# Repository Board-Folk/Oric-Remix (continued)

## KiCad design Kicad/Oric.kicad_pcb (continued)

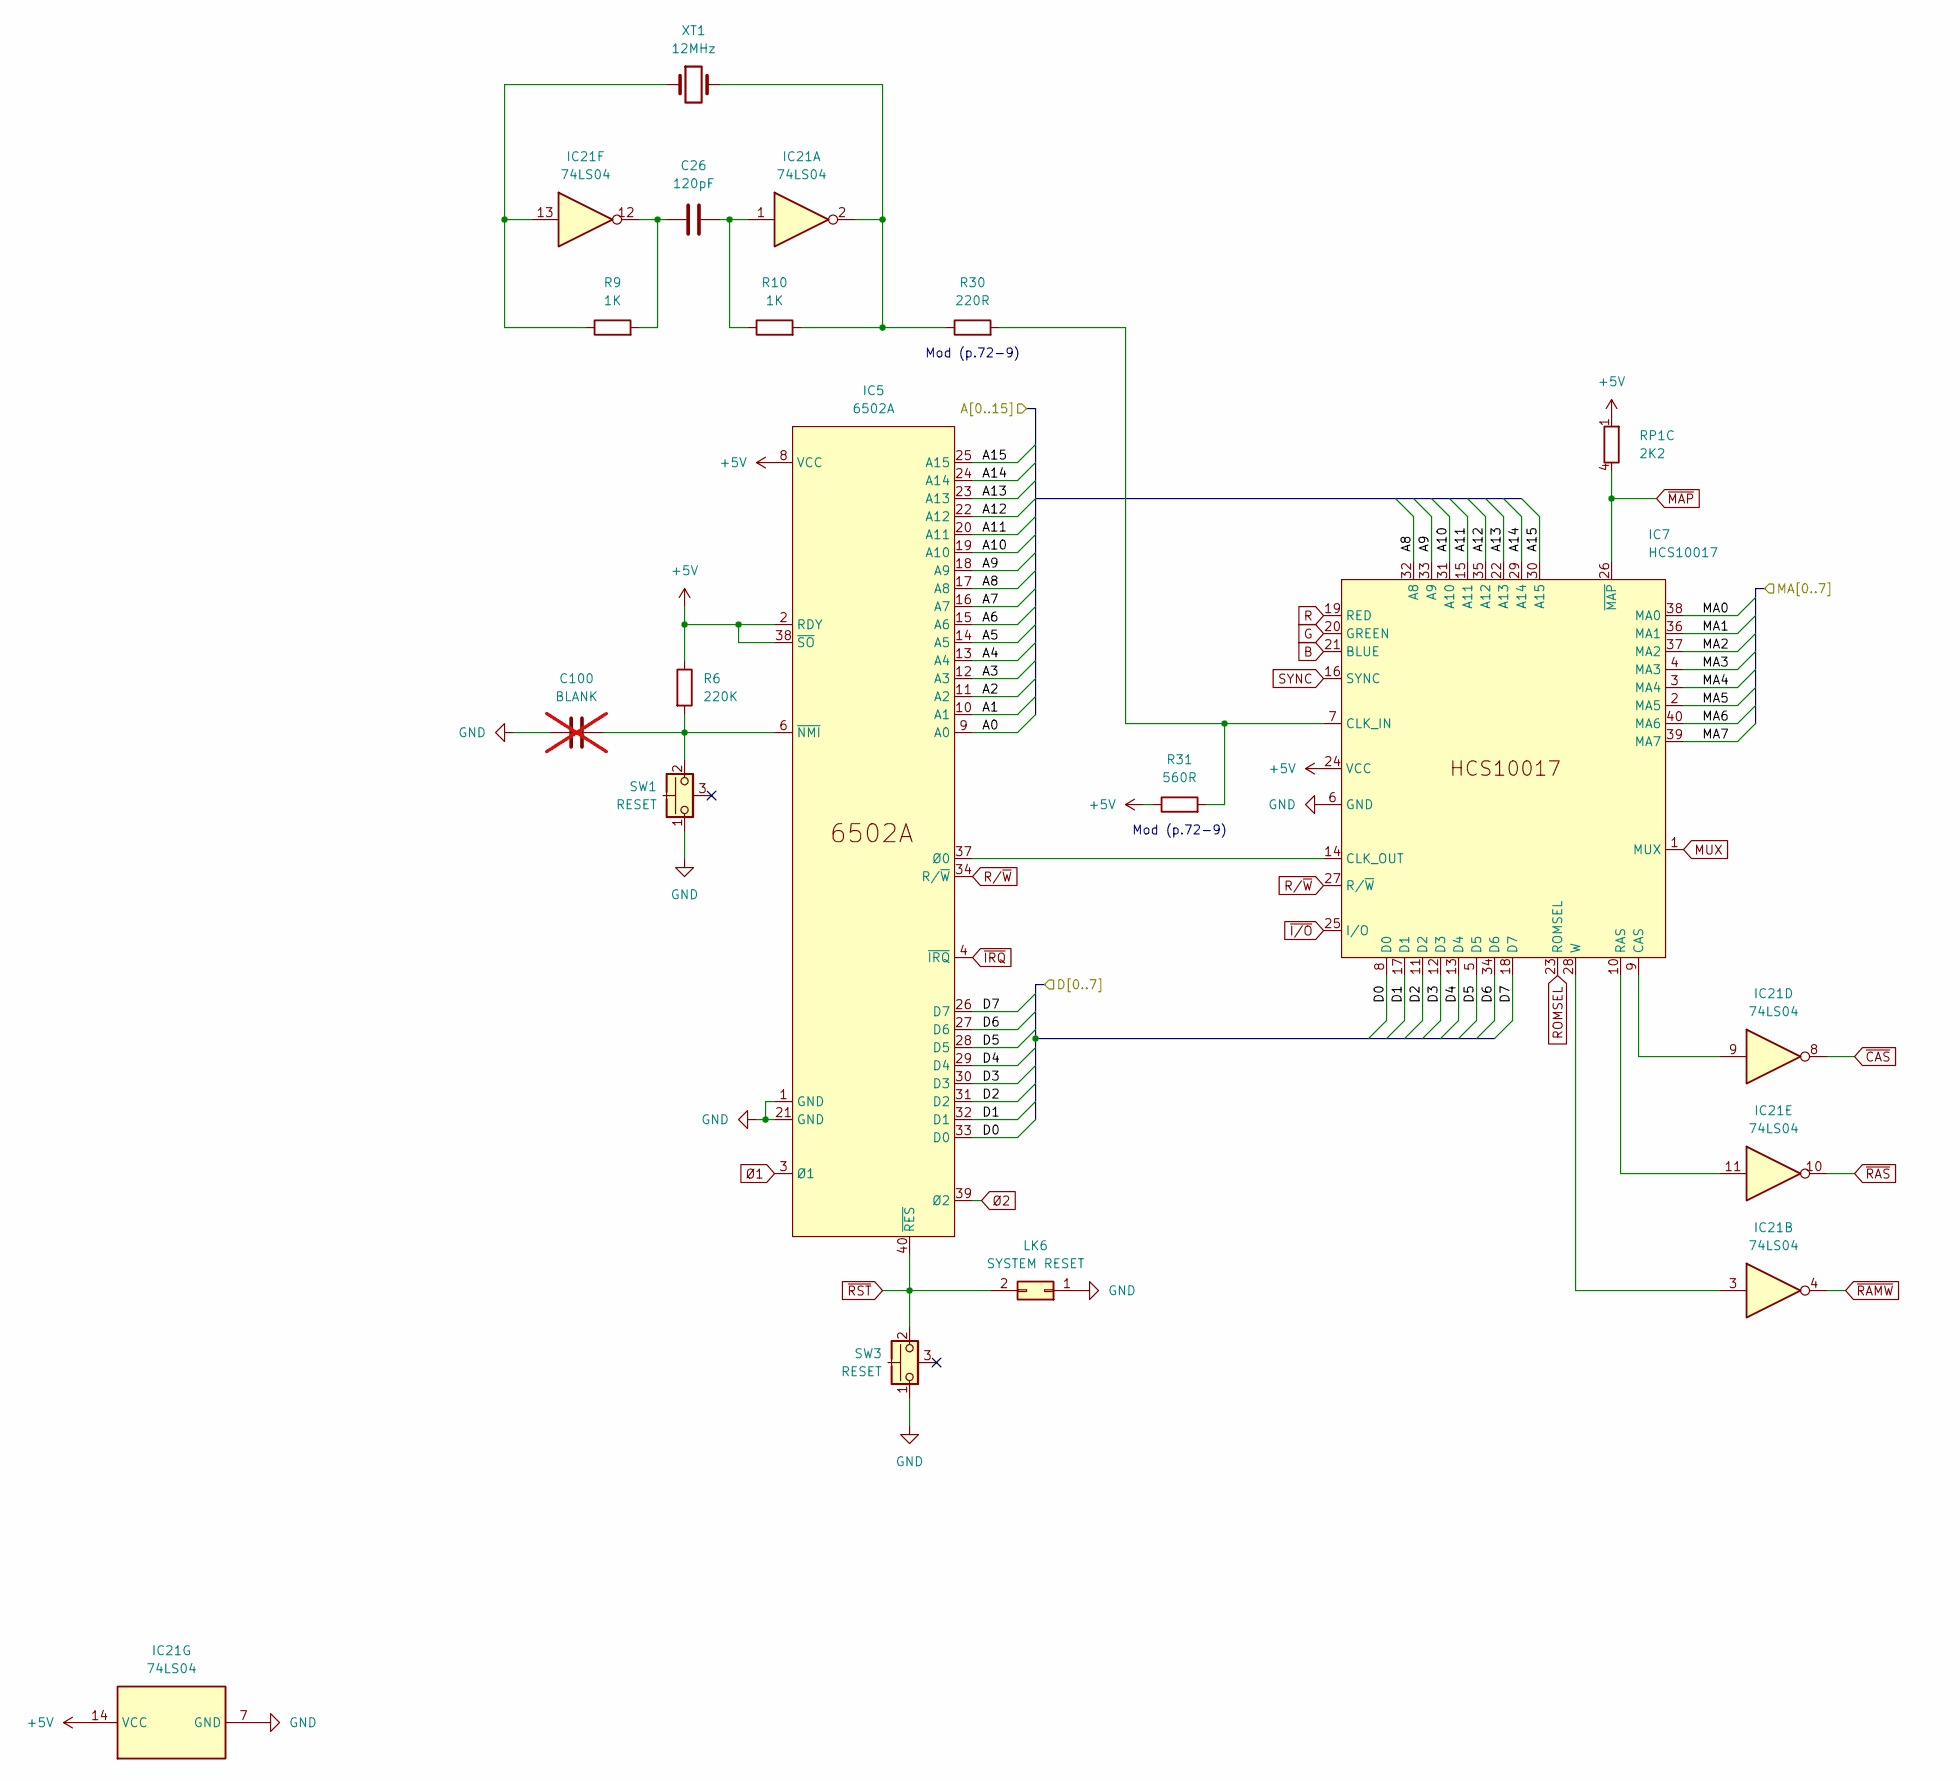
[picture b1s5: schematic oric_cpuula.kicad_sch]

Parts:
C26: 120pF; Ceramic Capacitor 5.00mm
C100: BLANK; Ceramic Capacitor 5.00mm_Blank; not fitted
IC5: 6502A; DIP-40_W15.24mm
IC7: HCS10017; DIP-40_W15.24mm
IC21: 74LS04; DIP-14_W7.62mm
LK6: SYSTEM RESET; PinHeader_1x02_P2.54mm
R6: 220K; Resistor 10.16mm
R9, R10: 1K; Resistor 10.16mm
R30: 220R; Resistor 10.16mm
R31: 560R; Resistor 10.16mm
RP1: 2K2; R_Array_SIP8_Bussed
SW1: RESET; Push Switch
SW3: RESET; Push Switch Simple
XT1: 12MHz; Crystal

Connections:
+5V: IC5.2 (RDY), IC5.8 (VCC), IC5.38 (~SO), IC7.24 (VCC), IC21.14 (VCC), R6.1, R31.1, RP1.1 (R1); also elsewhere on the board
/CPU and ULA/A0: IC5.9 (A0); also elsewhere on the board
/CPU and ULA/A1: IC5.10 (A1); also elsewhere on the board
/CPU and ULA/A2: IC5.11 (A2); also elsewhere on the board
/CPU and ULA/A3: IC5.12 (A3); also elsewhere on the board
/CPU and ULA/A4: IC5.13 (A4); also elsewhere on the board
/CPU and ULA/A5: IC5.14 (A5); also elsewhere on the board
/CPU and ULA/A6: IC5.15 (A6); also elsewhere on the board
/CPU and ULA/A7: IC5.16 (A7); also elsewhere on the board
/CPU and ULA/A8: IC5.17 (A8), IC7.32 (A8); also elsewhere on the board
/CPU and ULA/A9: IC5.18 (A9), IC7.33 (A9); also elsewhere on the board
/CPU and ULA/A10: IC5.19 (A10), IC7.31 (A10); also elsewhere on the board
/CPU and ULA/A11: IC5.20 (A11), IC7.15 (A11); also elsewhere on the board
/CPU and ULA/A12: IC5.22 (A12), IC7.35 (A12); also elsewhere on the board
/CPU and ULA/A13: IC5.23 (A13), IC7.22 (A13); also elsewhere on the board
/CPU and ULA/A14: IC5.24 (A14), IC7.29 (A14); also elsewhere on the board
/CPU and ULA/A15: IC5.25 (A15), IC7.30 (A15); also elsewhere on the board
/CPU and ULA/D0: IC5.33 (D0), IC7.8 (D0); also elsewhere on the board
/CPU and ULA/D1: IC5.32 (D1), IC7.17 (D1); also elsewhere on the board
/CPU and ULA/D2: IC5.31 (D2), IC7.11 (D2); also elsewhere on the board
/CPU and ULA/D3: IC5.30 (D3), IC7.12 (D3); also elsewhere on the board
/CPU and ULA/D4: IC5.29 (D4), IC7.13 (D4); also elsewhere on the board
/CPU and ULA/D5: IC5.28 (D5), IC7.5 (D5); also elsewhere on the board
/CPU and ULA/D6: IC5.27 (D6), IC7.34 (D6); also elsewhere on the board
/CPU and ULA/D7: IC5.26 (D7), IC7.18 (D7); also elsewhere on the board
/CPU and ULA/MA0: IC7.38 (MA0); also elsewhere on the board
/CPU and ULA/MA1: IC7.36 (MA1); also elsewhere on the board
/CPU and ULA/MA2: IC7.37 (MA2); also elsewhere on the board
/CPU and ULA/MA3: IC7.4 (MA3); also elsewhere on the board
/CPU and ULA/MA4: IC7.3 (MA4); also elsewhere on the board
/CPU and ULA/MA5: IC7.2 (MA5); also elsewhere on the board
/CPU and ULA/MA6: IC7.40 (MA6); also elsewhere on the board
/CPU and ULA/MA7: IC7.39 (MA7); also elsewhere on the board
B: IC7.21 (BLUE); also elsewhere on the board
G: IC7.20 (GREEN); also elsewhere on the board
GND: C100.1, IC5.1 (GND), IC5.21 (GND), IC7.6 (GND), IC21.7 (GND), LK6.1, SW1.1, SW3.1; also elsewhere on the board
MUX: IC7.1 (MUX); also elsewhere on the board
unnamed: C26.1, IC21.12, R9.2
unnamed: C26.2, IC21.1, R10.1
unnamed: C100.2, IC5.6 (~NMI), R6.2, SW1.2
unnamed: IC5.37 (Ø0), IC7.14 (CLK_OUT)
unnamed: IC7.9 (CAS), IC21.9
unnamed: IC7.7 (CLK_IN), R30.2, R31.2
unnamed: IC7.10 (RAS), IC21.11
unnamed: IC7.28 (W), IC21.3
unnamed: IC21.2, R10.2, R30.1, XT1.2
unnamed: IC21.13, R9.1, XT1.1
R: IC7.19 (RED); also elsewhere on the board
ROMSEL: IC7.23 (ROMSEL); also elsewhere on the board
R/~W: IC5.34 (R/~W), IC7.27 (R/~W); also elsewhere on the board
SYNC: IC7.16 (SYNC); also elsewhere on the board
~CAS: IC21.8; also elsewhere on the board
~IRQ: IC5.4 (~IRQ); also elsewhere on the board
~I/O: IC7.25 (I/O); also elsewhere on the board
~MAP: IC7.26 (~MAP), RP1.4 (R3.2); also elsewhere on the board
~RAMW: IC21.4; also elsewhere on the board
~RAS: IC21.10; also elsewhere on the board
~RST: IC5.40 (~RES), LK6.2, SW3.2; also elsewhere on the board
Ø1: IC5.3 (Ø1); also elsewhere on the board
Ø2: IC5.39 (Ø2); also elsewhere on the board

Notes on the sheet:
Mod (p.72-9)

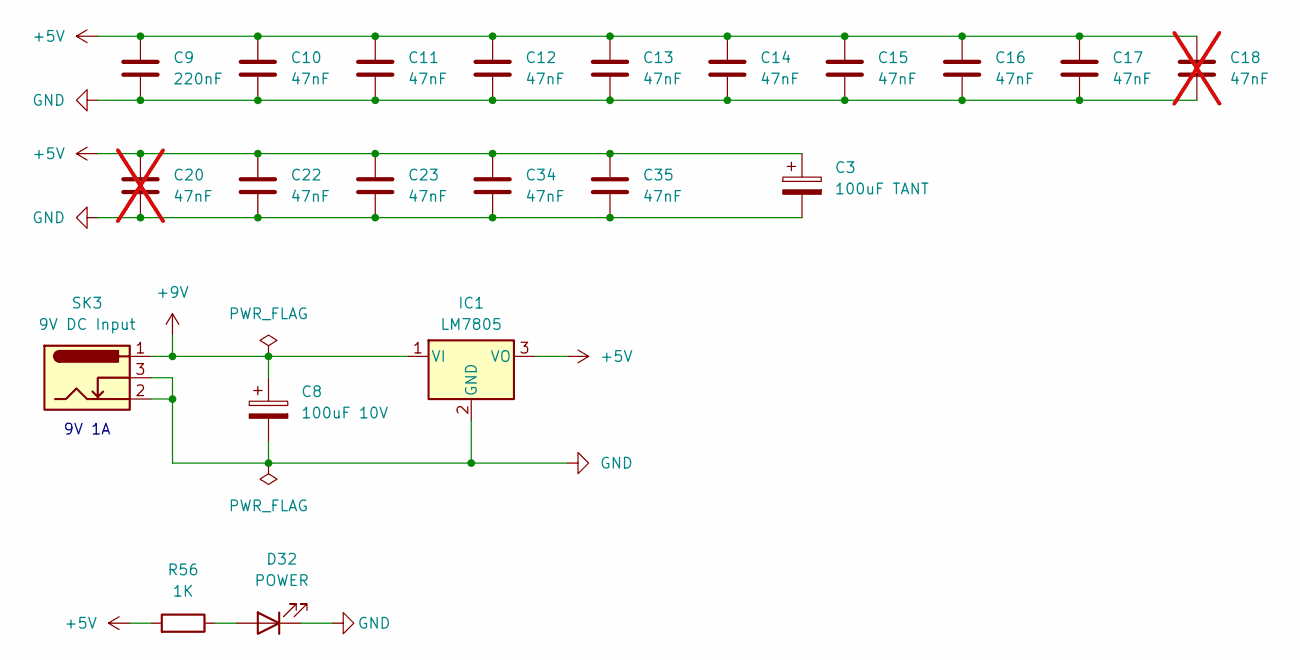
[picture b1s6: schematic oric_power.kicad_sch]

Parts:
C3: 100uF TANT; Tantalum Capacitor 5.00mm
C8: 100uF 10V; Electrolytic Capacitor 5.00mm
C9: 220nF; Ceramic Capacitor 5.00mm
C10, C11, C12, C13, C14, C15, C16, C17, C22, C23, C34, C35: 47nF; Ceramic Capacitor 5.00mm
C18, C20: 47nF; Ceramic Capacitor 5.00mm; not fitted
D32: POWER; LED_D3.0mm
IC1: LM7805; IC1 7805
R56: 1K; Resistor 10.16mm
SK3: 9V DC Input; SK3 Barrel Jack

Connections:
+5V: C3.1, C9.1, C10.1, C11.1, C12.1, C13.1, C14.1, C15.1, C16.1, C17.1, C18.1, C20.1, C22.1, C23.1, C34.1, C35.1, IC1.3 (VO), R56.2; also elsewhere on the board
+9V: C8.1, IC1.1 (VI), SK3.1; also elsewhere on the board
GND: C3.2, C8.2, C9.2, C10.2, C11.2, C12.2, C13.2, C14.2, C15.2, C16.2, C17.2, C18.2, C20.2, C22.2, C23.2, C34.2, C35.2, D32.1 (K), IC1.2 (GND), SK3.2, SK3.3; also elsewhere on the board
unnamed: D32.2 (A), R56.1

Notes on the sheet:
9V 1A

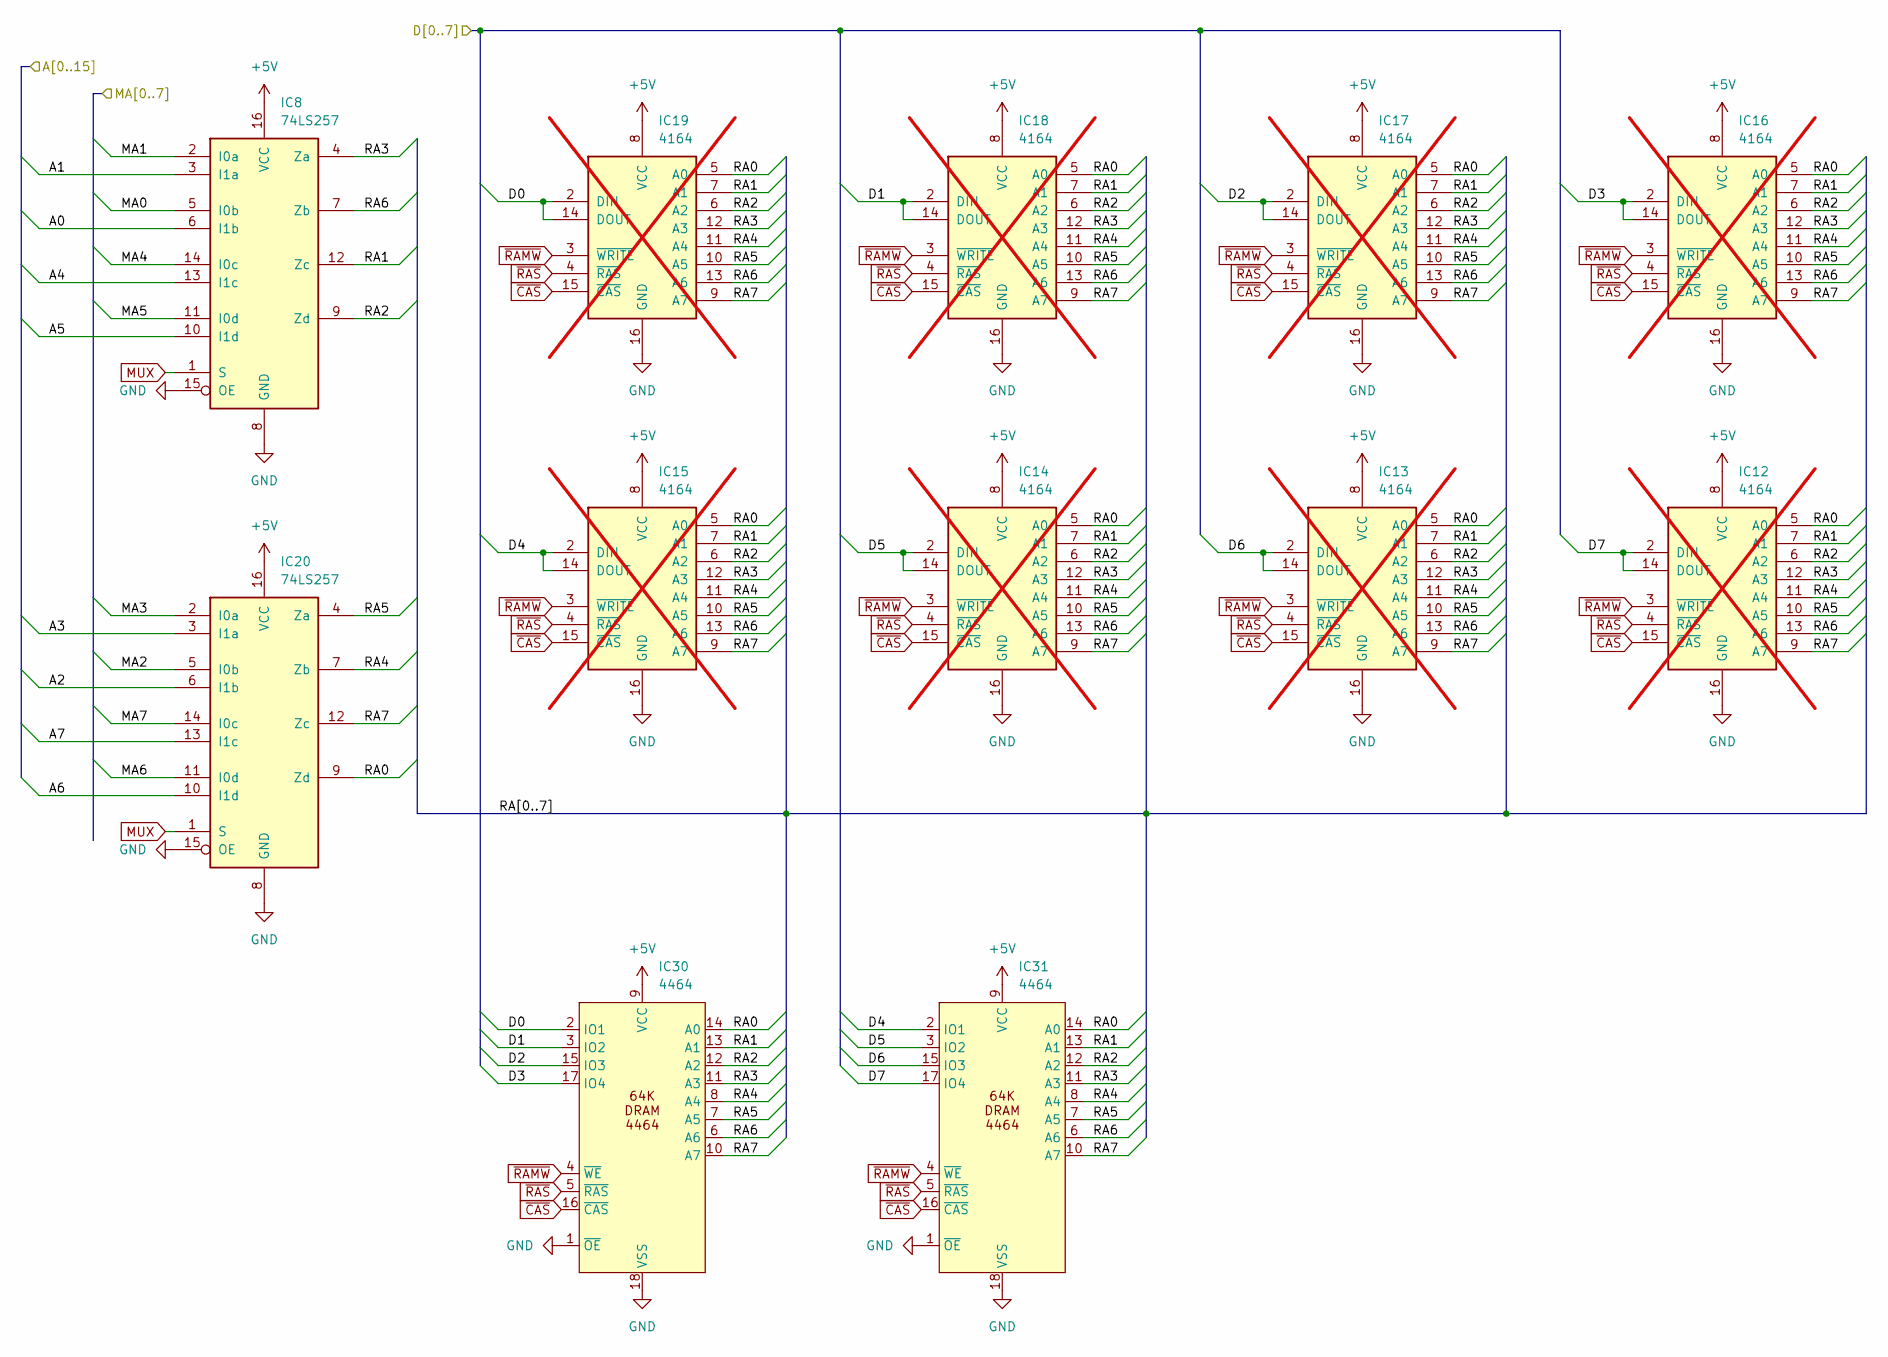
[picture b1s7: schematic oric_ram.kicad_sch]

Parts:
IC8, IC20: 74LS257; DIP-16_W7.62mm
IC12, IC13, IC14, IC15, IC16, IC17, IC18, IC19: 4164; DIP-16_W7.62mm; not fitted
IC30, IC31: 4464; DIP-18_W7.62mm

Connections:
+5V: IC8.16 (VCC), IC12.8 (VCC), IC13.8 (VCC), IC14.8 (VCC), IC15.8 (VCC), IC16.8 (VCC), IC17.8 (VCC), IC18.8 (VCC), IC19.8 (VCC), IC20.16 (VCC), IC30.9 (VCC), IC31.9 (VCC); also elsewhere on the board
/CPU and ULA/A0: IC8.6 (I1b); also elsewhere on the board
/CPU and ULA/A1: IC8.3 (I1a); also elsewhere on the board
/CPU and ULA/A2: IC20.6 (I1b); also elsewhere on the board
/CPU and ULA/A3: IC20.3 (I1a); also elsewhere on the board
/CPU and ULA/A4: IC8.13 (I1c); also elsewhere on the board
/CPU and ULA/A5: IC8.10 (I1d); also elsewhere on the board
/CPU and ULA/A6: IC20.10 (I1d); also elsewhere on the board
/CPU and ULA/A7: IC20.13 (I1c); also elsewhere on the board
/CPU and ULA/D0: IC19.2 (DIN), IC19.14 (DOUT), IC30.2 (IO1); also elsewhere on the board
/CPU and ULA/D1: IC18.2 (DIN), IC18.14 (DOUT), IC30.3 (IO2); also elsewhere on the board
/CPU and ULA/D2: IC17.2 (DIN), IC17.14 (DOUT), IC30.15 (IO3); also elsewhere on the board
/CPU and ULA/D3: IC16.2 (DIN), IC16.14 (DOUT), IC30.17 (IO4); also elsewhere on the board
/CPU and ULA/D4: IC15.2 (DIN), IC15.14 (DOUT), IC31.2 (IO1); also elsewhere on the board
/CPU and ULA/D5: IC14.2 (DIN), IC14.14 (DOUT), IC31.3 (IO2); also elsewhere on the board
/CPU and ULA/D6: IC13.2 (DIN), IC13.14 (DOUT), IC31.15 (IO3); also elsewhere on the board
/CPU and ULA/D7: IC12.2 (DIN), IC12.14 (DOUT), IC31.17 (IO4); also elsewhere on the board
/CPU and ULA/MA0: IC8.5 (I0b); also elsewhere on the board
/CPU and ULA/MA1: IC8.2 (I0a); also elsewhere on the board
/CPU and ULA/MA2: IC20.5 (I0b); also elsewhere on the board
/CPU and ULA/MA3: IC20.2 (I0a); also elsewhere on the board
/CPU and ULA/MA4: IC8.14 (I0c); also elsewhere on the board
/CPU and ULA/MA5: IC8.11 (I0d); also elsewhere on the board
/CPU and ULA/MA6: IC20.11 (I0d); also elsewhere on the board
/CPU and ULA/MA7: IC20.14 (I0c); also elsewhere on the board
/RAM/RA0: IC12.5 (A0), IC13.5 (A0), IC14.5 (A0), IC15.5 (A0), IC16.5 (A0), IC17.5 (A0), IC18.5 (A0), IC19.5 (A0), IC20.9 (Zd), IC30.14 (A0), IC31.14 (A0)
/RAM/RA1: IC8.12 (Zc), IC12.7 (A1), IC13.7 (A1), IC14.7 (A1), IC15.7 (A1), IC16.7 (A1), IC17.7 (A1), IC18.7 (A1), IC19.7 (A1), IC30.13 (A1), IC31.13 (A1)
/RAM/RA2: IC8.9 (Zd), IC12.6 (A2), IC13.6 (A2), IC14.6 (A2), IC15.6 (A2), IC16.6 (A2), IC17.6 (A2), IC18.6 (A2), IC19.6 (A2), IC30.12 (A2), IC31.12 (A2)
/RAM/RA3: IC8.4 (Za), IC12.12 (A3), IC13.12 (A3), IC14.12 (A3), IC15.12 (A3), IC16.12 (A3), IC17.12 (A3), IC18.12 (A3), IC19.12 (A3), IC30.11 (A3), IC31.11 (A3)
/RAM/RA4: IC12.11 (A4), IC13.11 (A4), IC14.11 (A4), IC15.11 (A4), IC16.11 (A4), IC17.11 (A4), IC18.11 (A4), IC19.11 (A4), IC20.7 (Zb), IC30.8 (A4), IC31.8 (A4)
/RAM/RA5: IC12.10 (A5), IC13.10 (A5), IC14.10 (A5), IC15.10 (A5), IC16.10 (A5), IC17.10 (A5), IC18.10 (A5), IC19.10 (A5), IC20.4 (Za), IC30.7 (A5), IC31.7 (A5)
/RAM/RA6: IC8.7 (Zb), IC12.13 (A6), IC13.13 (A6), IC14.13 (A6), IC15.13 (A6), IC16.13 (A6), IC17.13 (A6), IC18.13 (A6), IC19.13 (A6), IC30.6 (A6), IC31.6 (A6)
/RAM/RA7: IC12.9 (A7), IC13.9 (A7), IC14.9 (A7), IC15.9 (A7), IC16.9 (A7), IC17.9 (A7), IC18.9 (A7), IC19.9 (A7), IC20.12 (Zc), IC30.10 (A7), IC31.10 (A7)
GND: IC8.8 (GND), IC8.15 (OE), IC12.16 (GND), IC13.16 (GND), IC14.16 (GND), IC15.16 (GND), IC16.16 (GND), IC17.16 (GND), IC18.16 (GND), IC19.16 (GND), IC20.8 (GND), IC20.15 (OE), IC30.1 (~OE), IC30.18 (VSS), IC31.1 (~OE), IC31.18 (VSS); also elsewhere on the board
MUX: IC8.1 (S), IC20.1 (S); also elsewhere on the board
~CAS: IC12.15 (~CAS), IC13.15 (~CAS), IC14.15 (~CAS), IC15.15 (~CAS), IC16.15 (~CAS), IC17.15 (~CAS), IC18.15 (~CAS), IC19.15 (~CAS), IC30.16 (~CAS), IC31.16 (~CAS); also elsewhere on the board
~RAMW: IC12.3 (~WRITE), IC13.3 (~WRITE), IC14.3 (~WRITE), IC15.3 (~WRITE), IC16.3 (~WRITE), IC17.3 (~WRITE), IC18.3 (~WRITE), IC19.3 (~WRITE), IC30.4 (~WE), IC31.4 (~WE); also elsewhere on the board
~RAS: IC12.4 (~RAS), IC13.4 (~RAS), IC14.4 (~RAS), IC15.4 (~RAS), IC16.4 (~RAS), IC17.4 (~RAS), IC18.4 (~RAS), IC19.4 (~RAS), IC30.5 (~RAS), IC31.5 (~RAS); also elsewhere on the board

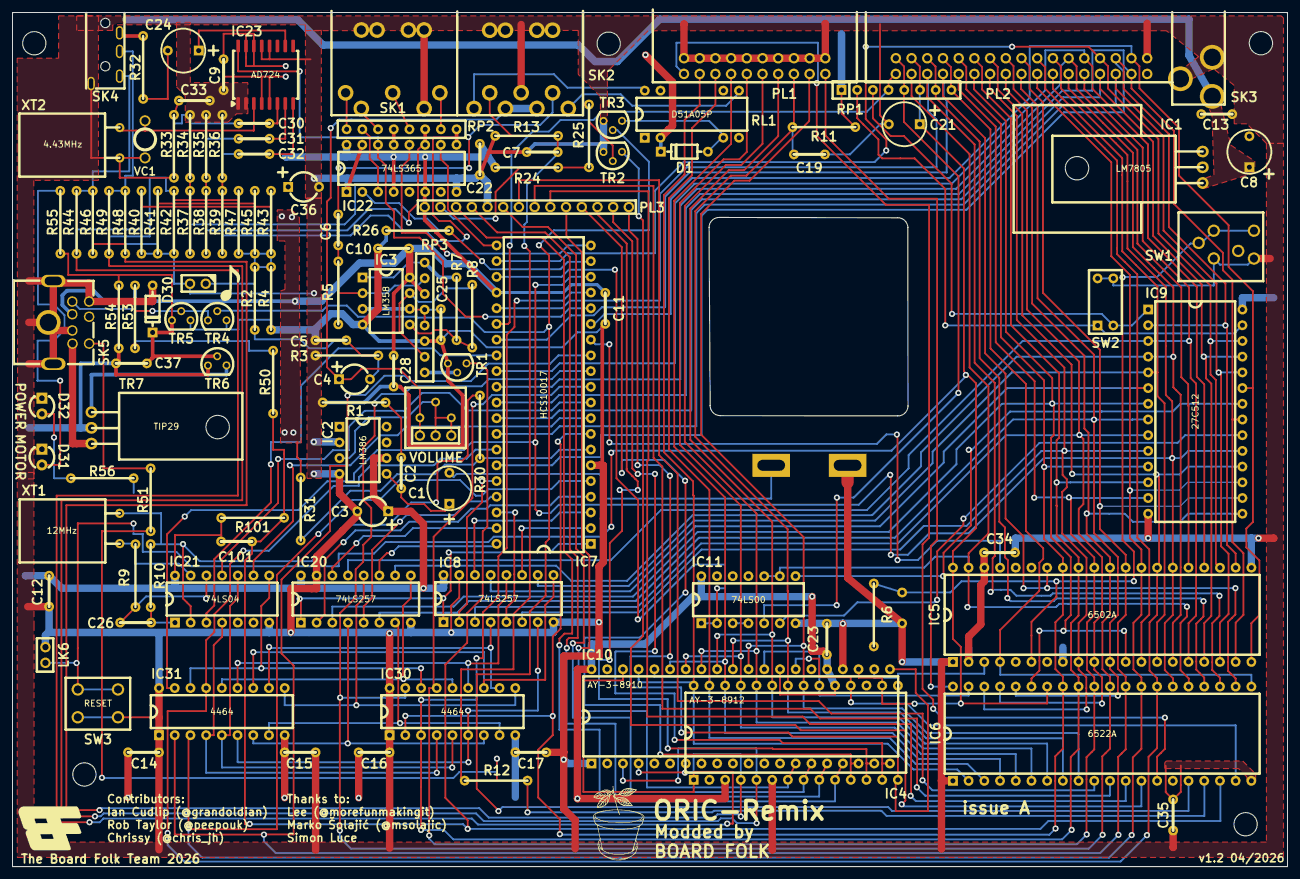
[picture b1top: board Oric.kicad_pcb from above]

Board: 2 copper layers, 206.2 x 138.1 mm, 132 parts (1 on the bottom side), 155 nets.

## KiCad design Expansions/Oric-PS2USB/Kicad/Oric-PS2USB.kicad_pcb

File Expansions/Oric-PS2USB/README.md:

# Oric-PS2USB

This is currently a prototype board to prove the schematic and code for doing something a bit better. The board contains footprints for both the Arduino Nano and Mini-DIN socket for PS/2 and the Seediuno Xiao for USB. Only populate one or the other.

It won't fit in an original case - it's not intended for that. It's suitable to get going with the Oric if you've no keyboard available - board only if you like. Better than no keyboard at all. The main board will need a 14 pin header fitting with pins long enough to reach the socket, approx 14mm above the component side of the board.

So far only the code for the Nano PS/2 assembly has been completed.

In the future, alongside more useful maybe a much reduced version in size we'll also do an MX keyboard similar to that of the Atmos - though this has already been done by others if you Google.

## BOM

The BOM is quite simple.

### PS/2

|Qty|Reference(s)|Value|Type|Notes|
|:--:|:--:|:--:|:--:|:--:|
|1|C1|47nF|Ceramic||
|1|C2|47uF|Electrolytic||
|1|R1|470R|Resistor||
|1|R2|10K|Resistor||
|1|D17|LED|3MM LED||
|1|U1|MT8816AE1|IC|DIP-40 Version|
|1|U2|Nano|Arduino||
|1|U3|CD4051|IC||
|1|PL1|14 pin socket|Socket Header||
|1|J3|6 pin Mini-DIN Socket|PS/2 Socket||

### USB

To follow.

## Code

The Arduino folder contains the code for the PS/2 interface and can be loaded with Arduino IDE. This is based on C64Keyboard by Robert VanHazinga. Key mappings can be found in keymapping.h - these are calculated from the spreadsheet "orickeyboard.ods" also in the Arduino folder.

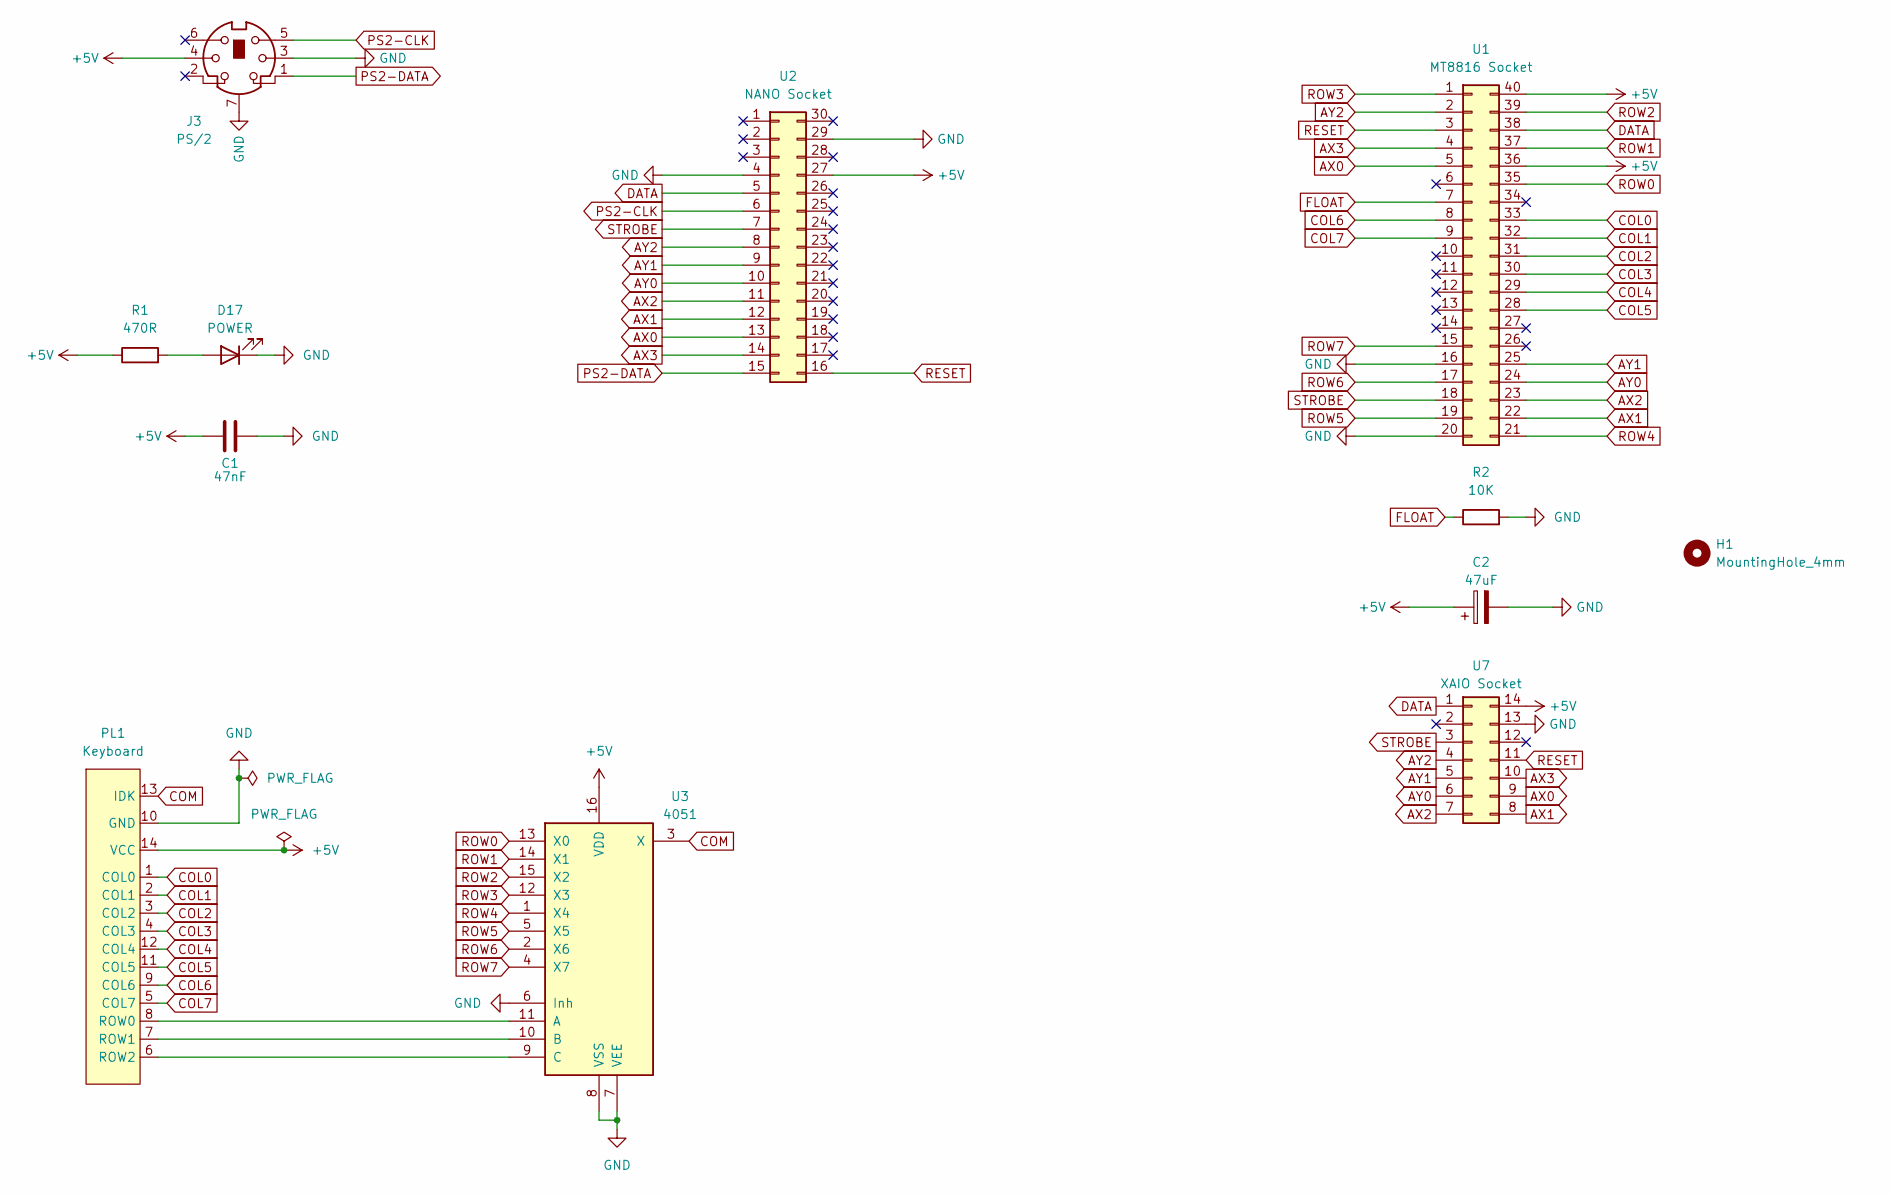
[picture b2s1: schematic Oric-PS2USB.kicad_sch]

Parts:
C1: 47nF; C_Disc_D4.3mm_W1.9mm_P5.00mm
C2: 47uF; CP_Radial_D5.0mm_P2.00mm
D17: POWER; LED_D3.0mm
H1: MountingHole_4mm
J3: PS/2; Connector_Mini-DIN_Female_6Pin_2rows
PL1: Keyboard; PinHeader_1x14_P2.54mm_Vertical
R1: 470R; R_Axial_DIN0204_L3.6mm_D1.6mm_P7.62mm_Horizontal
R2: 10K; R_Axial_DIN0204_L3.6mm_D1.6mm_P7.62mm_Horizontal
U1: MT8816 Socket; DIP-40_W15.24mm_Socket
U2: NANO Socket; Arduino_Nano_WithMountingHoles
U3: 4051; DIP-16_W7.62mm
U7: XAIO Socket; XAIO 14PIN

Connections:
+5V: C1.2, C2.1, J3.4, PL1.14 (VCC), R1.1, U1.36, U1.40, U2.27, U3.16 (VDD), U7.14
AX0: U1.5, U2.13, U7.9
AX1: U1.22, U2.12, U7.8
AX2: U1.23, U2.11, U7.7
AX3: U1.4, U2.14, U7.10
AY0: U1.24, U2.10, U7.6
AY1: U1.25, U2.9, U7.5
AY2: U1.2, U2.8, U7.4
COL0: PL1.1 (COL0), U1.33
COL1: PL1.2 (COL1), U1.32
COL2: PL1.3 (COL2), U1.31
COL3: PL1.4 (COL3), U1.30
COL4: PL1.12 (COL4), U1.29
COL5: PL1.11 (COL5), U1.28
COL6: PL1.9 (COL6), U1.8
COL7: PL1.5 (COL7), U1.9
COM: PL1.13 (IDK), U3.3 (X)
DATA: U1.38, U2.5, U7.1
FLOAT: R2.1, U1.7
GND: C1.1, C2.2, D17.1 (K), J3.3, J3.7, PL1.10 (GND), R2.2, U1.16, U1.20, U2.4, U2.29, U3.6 (Inh), U3.7 (VEE), U3.8 (VSS), U7.13
unnamed: D17.2 (A), R1.2
unnamed: PL1.8 (ROW0), U3.11 (A)
unnamed: PL1.7 (ROW1), U3.10 (B)
unnamed: PL1.6 (ROW2), U3.9 (C)
PS2-CLK: J3.5, U2.6
PS2-DATA: J3.1, U2.15
RESET: U1.3, U2.16, U7.11
ROW0: U1.35, U3.13 (X0)
ROW1: U1.37, U3.14 (X1)
ROW2: U1.39, U3.15 (X2)
ROW3: U1.1, U3.12 (X3)
ROW4: U1.21, U3.1 (X4)
ROW5: U1.19, U3.5 (X5)
ROW6: U1.17, U3.2 (X6)
ROW7: U1.15, U3.4 (X7)
STROBE: U1.18, U2.7, U7.3

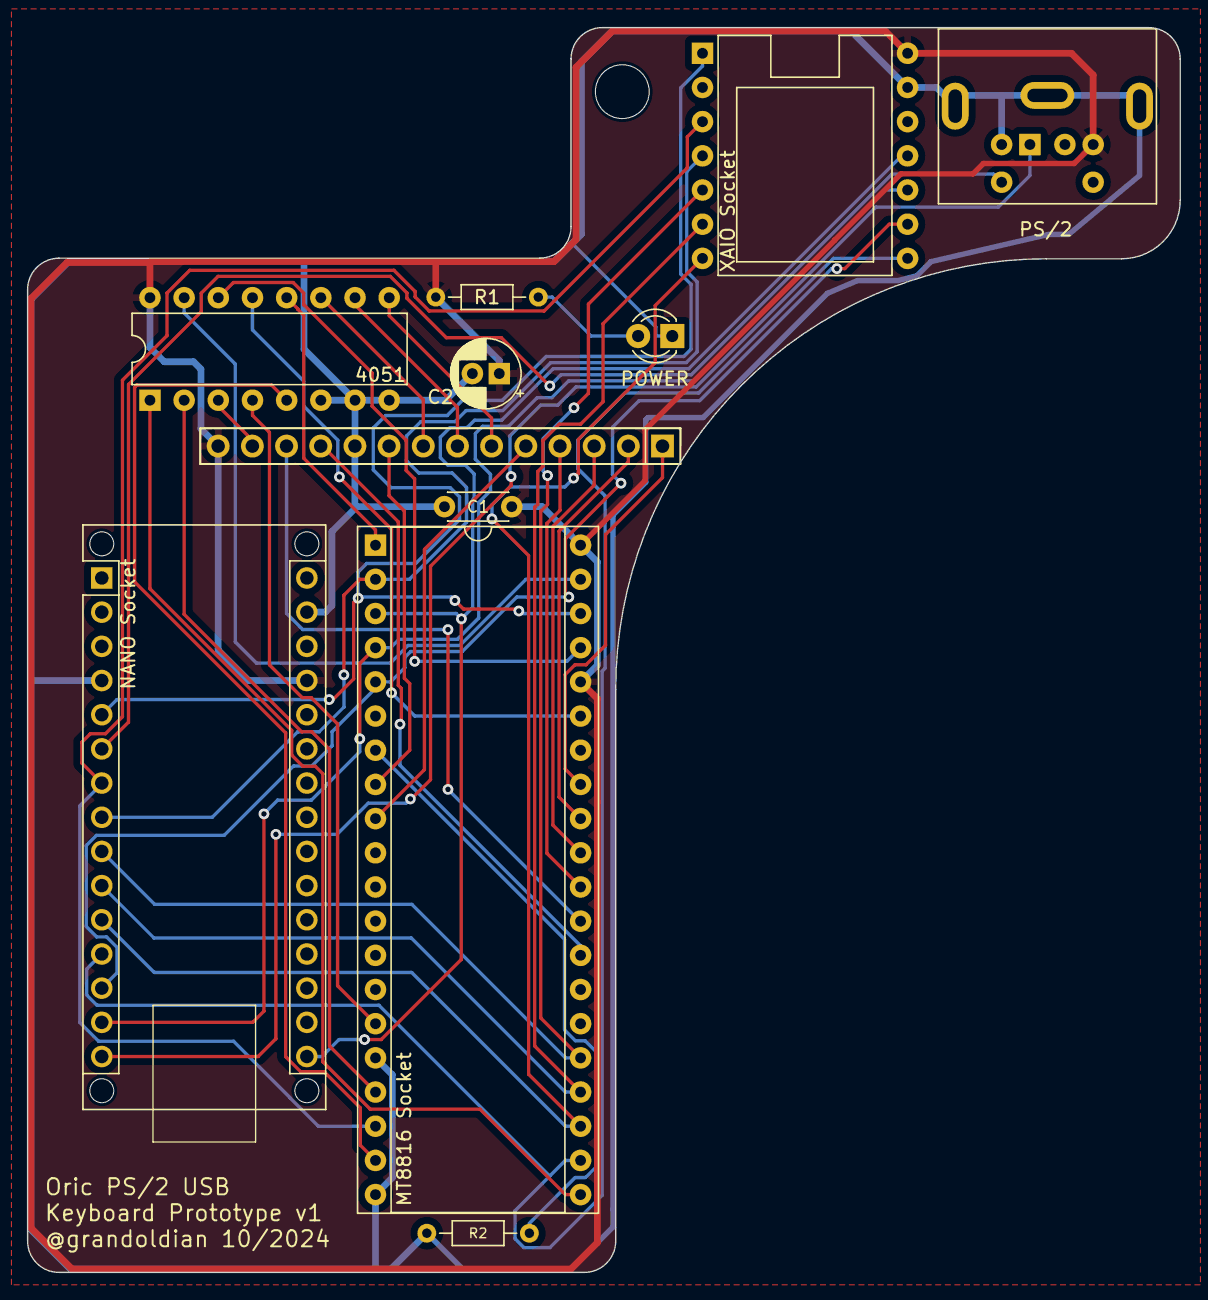
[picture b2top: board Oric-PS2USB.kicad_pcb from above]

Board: 2 copper layers, 85.7 x 92.5 mm, 12 parts (0 on the bottom side), 36 nets.

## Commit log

2025-02-05 Public rebase
2025-02-16 Oric-PS2USB
2026-05-06 Remix v1.2
